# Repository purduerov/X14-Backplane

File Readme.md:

# Readme for X14-Backplane

Whenever you make a new part, download the datasheet and save it here _**and**_ with the part in the parts library

Always pull other people's changes before beginning to work
`git pull`

Be sure to push your changes after  working on them. Run:
1. `git add .` to add any files in this directory or a subdirectory
or `git add -u` to add any modified files
2. (Optional) `git clean -nX` to see what ignored files can be removed
	`git clean -fX` removes ignored files (Eagle backups)
3. `git commit -m "helpful commit message"` with a description of the work that you did
4. `git push` to push your work to github

Other helpful commands
* `git status` says information about modified and staged files
* `git log` shows the recent commits of the repository
* `git log filename.extension` show the recent commits for just that file
* `git checkout first-couple-letter-of-commit-id` lets you go back to a previous version
* `git checkout master` brings you back to the latest commit
* `git tag` lists the tags
* `git tag -a orderX -m "the version of the board placed for the X'th order"` tag a specific commit
* `git push --tags` needed to push tags to remote
* `git show orderX` show the commit log for the given tag
* `git checkout orderX` go back and interact with the files at the tagged commit

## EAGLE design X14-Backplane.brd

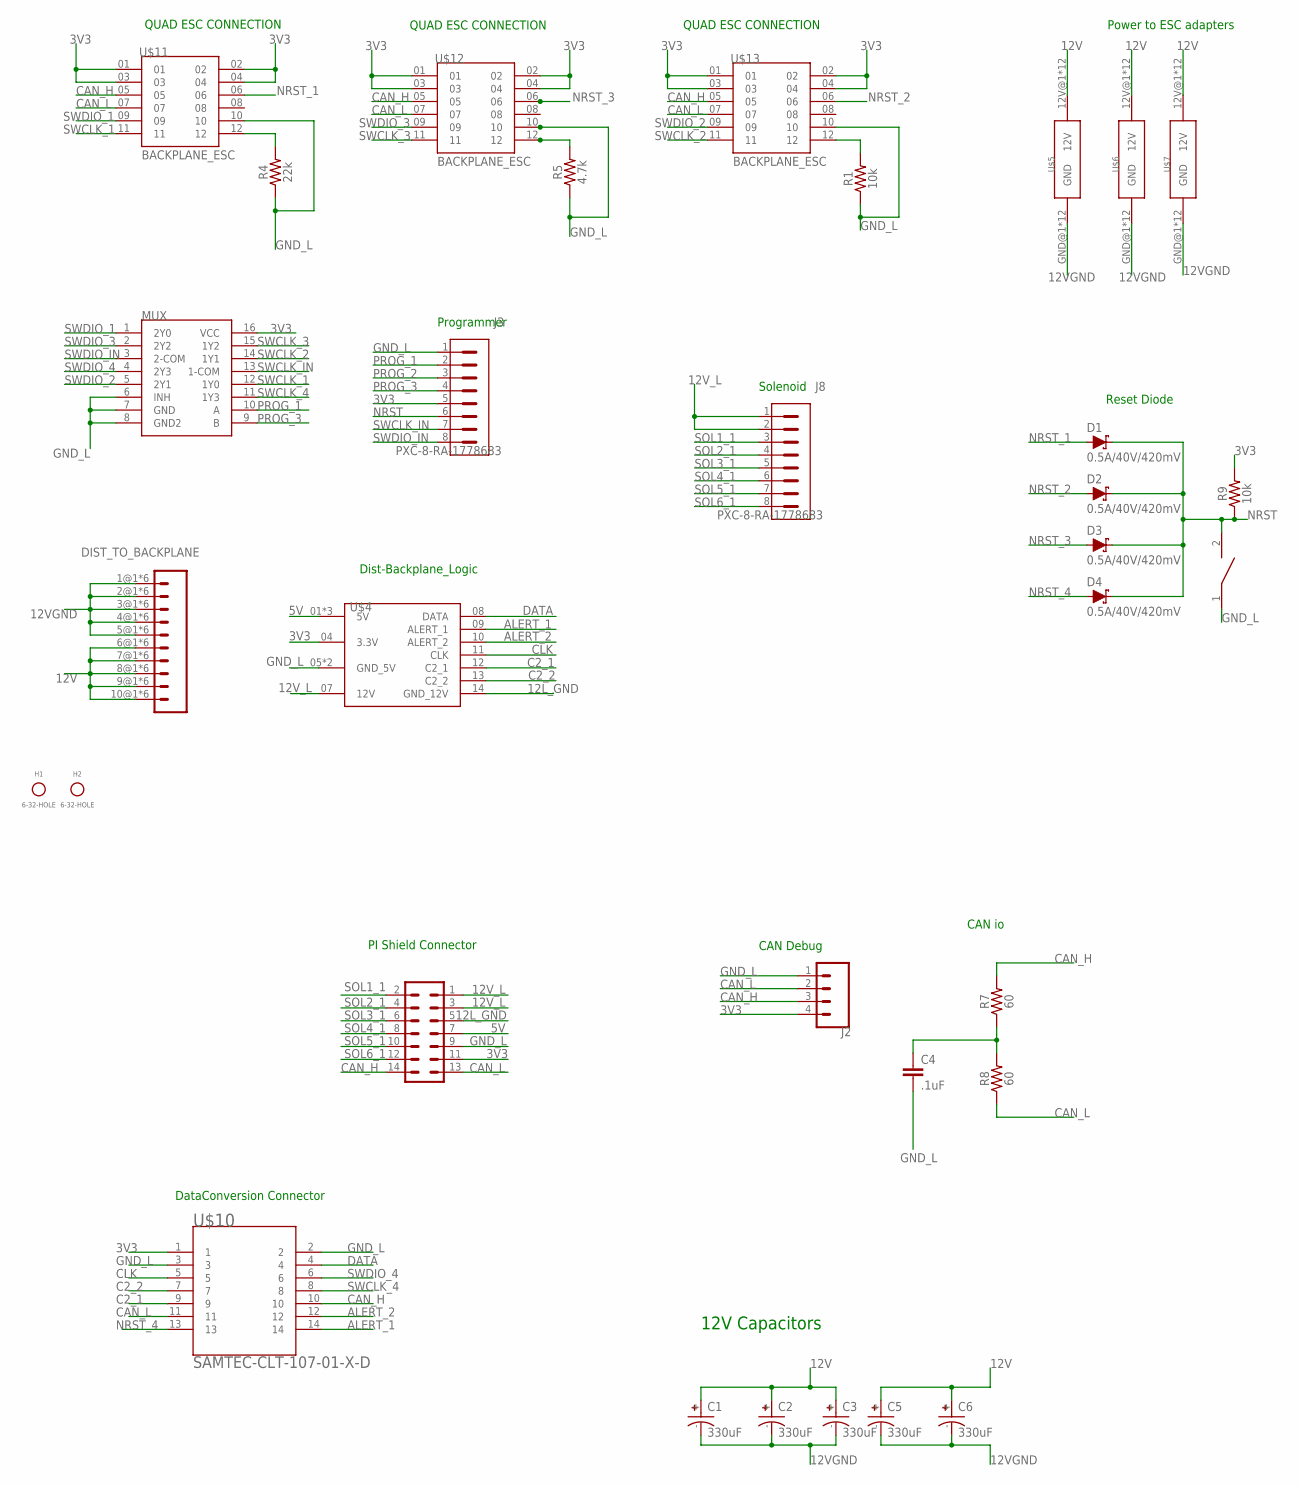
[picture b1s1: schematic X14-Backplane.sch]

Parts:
C1, C2, C3, C5, C6: 330uF; CAPAE1030X1050N
C4: .1uF; 0603
D1, D2, D3, D4: 0.5A/40V/420mV; SOD-323
DIST_TO_BACKPLANE: MPPT-10-01-01-L-RA-SD
H1, H2: 6-32-HOLE
J2: PXC-PTSM-04-RA-1778641
J3, J8: PXC-8-RA-1778683
MUX: TI-SN74LV4052A; SOIC-16
R1, R9: 10k; 0603
R4: 22k; 0603
R5: 4.7k; 0603
R7, R8: 60; 0603
U$4: BACKPLANE-DISTRIBUTION; SAMTEC_IPL1-107-01-X-D-K(B-D)
U$5, U$6, U$7: BACKPLANE_ESC_ADAPTER_PWRBKP; BACKPLANE_ESC_ADAPTER_BKP_PWR
U$8: DISCRETECOMPONENTS_SWITCH; DISCRETECOMPONENTS_SW_2512
U$9: 7X_CONN; IPL7X2
U$10: BACKPLANE->DATACONV; SAMTEC-CLT-107-01-X-D-BACKPLANE
U$11, U$12, U$13: BACKPLANE_ESC; SAMTEC_SQT-107-01-F-D

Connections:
3V3: J2.4, J3.5, MUX.16 (VCC), R9.2, U$4.04 (3.3V), U$9.11 (24), U$10.1, U$11.01, U$11.02, U$11.03, U$11.04, U$12.01, U$12.02, U$12.03, U$12.04, U$13.01, U$13.02, U$13.03, U$13.04
5V: U$4.01 (5V), U$4.02 (5V), U$4.03 (5V), U$9.7 (20)
12L_GND: U$4.14 (GND_12V), U$9.5 (18)
12V: C1.+, C2.+, C3.+, C5.+, C6.+, DIST_TO_BACKPLANE.6@1 (6), DIST_TO_BACKPLANE.6@2 (6), DIST_TO_BACKPLANE.6@3 (6), DIST_TO_BACKPLANE.6@4 (6), DIST_TO_BACKPLANE.6@5 (6), DIST_TO_BACKPLANE.6@6 (6), DIST_TO_BACKPLANE.7@1 (7), DIST_TO_BACKPLANE.7@2 (7), DIST_TO_BACKPLANE.7@3 (7), DIST_TO_BACKPLANE.7@4 (7), DIST_TO_BACKPLANE.7@5 (7), DIST_TO_BACKPLANE.7@6 (7), DIST_TO_BACKPLANE.8@1 (8), DIST_TO_BACKPLANE.8@2 (8), DIST_TO_BACKPLANE.8@3 (8), DIST_TO_BACKPLANE.8@4 (8), DIST_TO_BACKPLANE.8@5 (8), DIST_TO_BACKPLANE.8@6 (8), DIST_TO_BACKPLANE.9@1 (9), DIST_TO_BACKPLANE.9@2 (9), DIST_TO_BACKPLANE.9@3 (9), DIST_TO_BACKPLANE.9@4 (9), DIST_TO_BACKPLANE.9@5 (9), DIST_TO_BACKPLANE.9@6 (9), DIST_TO_BACKPLANE.10@1 (10), DIST_TO_BACKPLANE.10@2 (10), DIST_TO_BACKPLANE.10@3 (10), DIST_TO_BACKPLANE.10@4 (10), DIST_TO_BACKPLANE.10@5 (10), DIST_TO_BACKPLANE.10@6 (10), U$5.12V@1 (12V), U$5.12V@2 (12V), U$5.12V@3 (12V), U$5.12V@4 (12V), U$5.12V@5 (12V), U$5.12V@6 (12V), U$5.12V@7 (12V), U$5.12V@8 (12V), U$5.12V@9 (12V), U$5.12V@10 (12V), U$5.12V@11 (12V), U$5.12V@12 (12V), U$6.12V@1 (12V), U$6.12V@2 (12V), U$6.12V@3 (12V), U$6.12V@4 (12V), U$6.12V@5 (12V), U$6.12V@6 (12V), U$6.12V@7 (12V), U$6.12V@8 (12V), U$6.12V@9 (12V), U$6.12V@10 (12V), U$6.12V@11 (12V), U$6.12V@12 (12V), U$7.12V@1 (12V), U$7.12V@2 (12V), U$7.12V@3 (12V), U$7.12V@4 (12V), U$7.12V@5 (12V), U$7.12V@6 (12V), U$7.12V@7 (12V), U$7.12V@8 (12V), U$7.12V@9 (12V), U$7.12V@10 (12V), U$7.12V@11 (12V), U$7.12V@12 (12V)
12VGND: C1.-, C2.-, C3.-, C5.-, C6.-, DIST_TO_BACKPLANE.1@1 (1), DIST_TO_BACKPLANE.1@2 (1), DIST_TO_BACKPLANE.1@3 (1), DIST_TO_BACKPLANE.1@4 (1), DIST_TO_BACKPLANE.1@5 (1), DIST_TO_BACKPLANE.1@6 (1), DIST_TO_BACKPLANE.2@1 (2), DIST_TO_BACKPLANE.2@2 (2), DIST_TO_BACKPLANE.2@3 (2), DIST_TO_BACKPLANE.2@4 (2), DIST_TO_BACKPLANE.2@5 (2), DIST_TO_BACKPLANE.2@6 (2), DIST_TO_BACKPLANE.3@1 (3), DIST_TO_BACKPLANE.3@2 (3), DIST_TO_BACKPLANE.3@3 (3), DIST_TO_BACKPLANE.3@4 (3), DIST_TO_BACKPLANE.3@5 (3), DIST_TO_BACKPLANE.3@6 (3), DIST_TO_BACKPLANE.4@1 (4), DIST_TO_BACKPLANE.4@2 (4), DIST_TO_BACKPLANE.4@3 (4), DIST_TO_BACKPLANE.4@4 (4), DIST_TO_BACKPLANE.4@5 (4), DIST_TO_BACKPLANE.4@6 (4), DIST_TO_BACKPLANE.5@1 (5), DIST_TO_BACKPLANE.5@2 (5), DIST_TO_BACKPLANE.5@3 (5), DIST_TO_BACKPLANE.5@4 (5), DIST_TO_BACKPLANE.5@5 (5), DIST_TO_BACKPLANE.5@6 (5), U$5.GND@1 (GND), U$5.GND@2 (GND), U$5.GND@3 (GND), U$5.GND@4 (GND), U$5.GND@5 (GND), U$5.GND@6 (GND), U$5.GND@7 (GND), U$5.GND@8 (GND), U$5.GND@9 (GND), U$5.GND@10 (GND), U$5.GND@11 (GND), U$5.GND@12 (GND), U$6.GND@1 (GND), U$6.GND@2 (GND), U$6.GND@3 (GND), U$6.GND@4 (GND), U$6.GND@5 (GND), U$6.GND@6 (GND), U$6.GND@7 (GND), U$6.GND@8 (GND), U$6.GND@9 (GND), U$6.GND@10 (GND), U$6.GND@11 (GND), U$6.GND@12 (GND), U$7.GND@1 (GND), U$7.GND@2 (GND), U$7.GND@3 (GND), U$7.GND@4 (GND), U$7.GND@5 (GND), U$7.GND@6 (GND), U$7.GND@7 (GND), U$7.GND@8 (GND), U$7.GND@9 (GND), U$7.GND@10 (GND), U$7.GND@11 (GND), U$7.GND@12 (GND)
12V_L: J8.1, J8.2, U$4.07 (12V), U$9.1 (14), U$9.3 (16)
ALERT_1: U$4.09 (ALERT_1), U$10.14
ALERT_2: U$4.10 (ALERT_2), U$10.12
C2_1: U$4.12 (C2_1), U$10.9
C2_2: U$4.13 (C2_2), U$10.7
CAN_H: J2.3, R7.2, U$9.14 (2), U$10.10, U$11.05, U$12.05, U$13.05
CAN_L: J2.2, R8.1, U$9.13 (1), U$10.11, U$11.07, U$12.07, U$13.07
CLK: U$4.11 (CLK), U$10.5
DATA: U$4.08 (DATA), U$10.4
ESCID_1: R4.2, U$11.12
ESCID_2: R1.2, U$13.12
ESCID_3: R5.2, U$12.12
GND_L: C4.2, J2.1, J3.1, MUX.6 (INH), MUX.7 (GND), MUX.8 (GND2), R1.1, R4.1, R5.1, U$4.05 (GND_5V), U$4.06 (GND_5V), U$8.1, U$9.9 (22), U$10.2, U$10.3, U$11.10, U$12.10, U$13.10
unnamed: C4.1, R7.1, R8.2
NRST: D1.C, D2.C, D3.C, D4.C, J3.6, R9.1, U$8.2
NRST_1: D1.A, U$11.06
NRST_2: D2.A, U$13.06
NRST_3: D3.A, U$12.06
NRST_4: D4.A, U$10.13
PROG_1: J3.2, MUX.10 (A)
PROG_2: J3.3
PROG_3: J3.4, MUX.9 (B)
SOL1_1: J8.3, U$9.2 (13)
SOL2_1: J8.4, U$9.4 (15)
SOL3_1: J8.5, U$9.6 (17)
SOL4_1: J8.6, U$9.8 (19)
SOL5_1: J8.7, U$9.10 (21)
SOL6_1: J8.8, U$9.12 (23)
SWCLK_1: MUX.12 (1Y0), U$11.11
SWCLK_2: MUX.14 (1Y1), U$13.11
SWCLK_3: MUX.15 (1Y2), U$12.11
SWCLK_4: MUX.11 (1Y3), U$10.8
SWCLK_IN: J3.7, MUX.13 (1-COM)
SWDIO_1: MUX.1 (2Y0), U$11.09
SWDIO_2: MUX.5 (2Y1), U$13.09
SWDIO_3: MUX.2 (2Y2), U$12.09
SWDIO_4: MUX.4 (2Y3), U$10.6
SWDIO_IN: J3.8, MUX.3 (2-COM)

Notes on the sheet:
CAN Debug
Programmer
QUAD ESC CONNECTION
Dist-Backplane_Logic
Solenoid
Power to ESC adapters
Reset Diode
PI Shield Connector
CAN io
DataConversion Connector
12V Capacitors

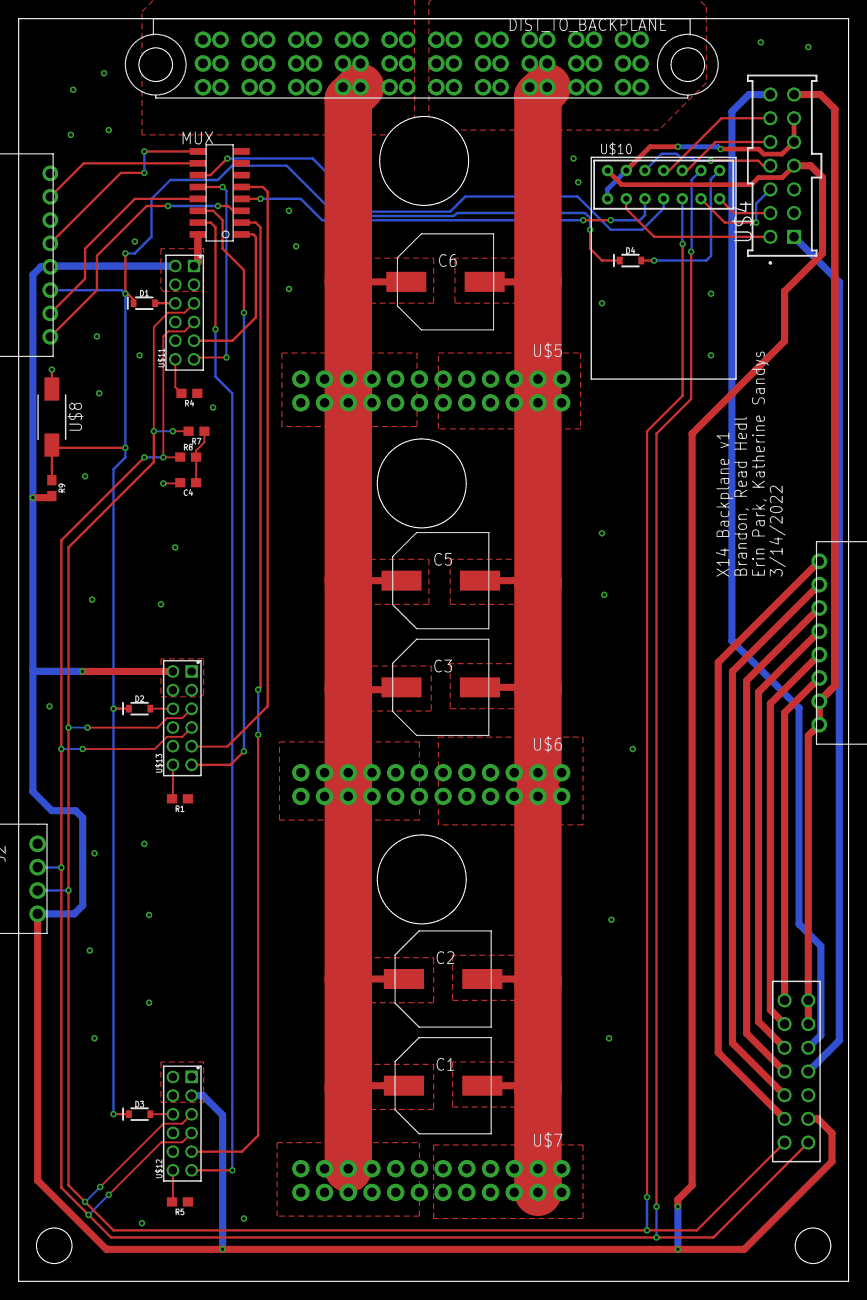
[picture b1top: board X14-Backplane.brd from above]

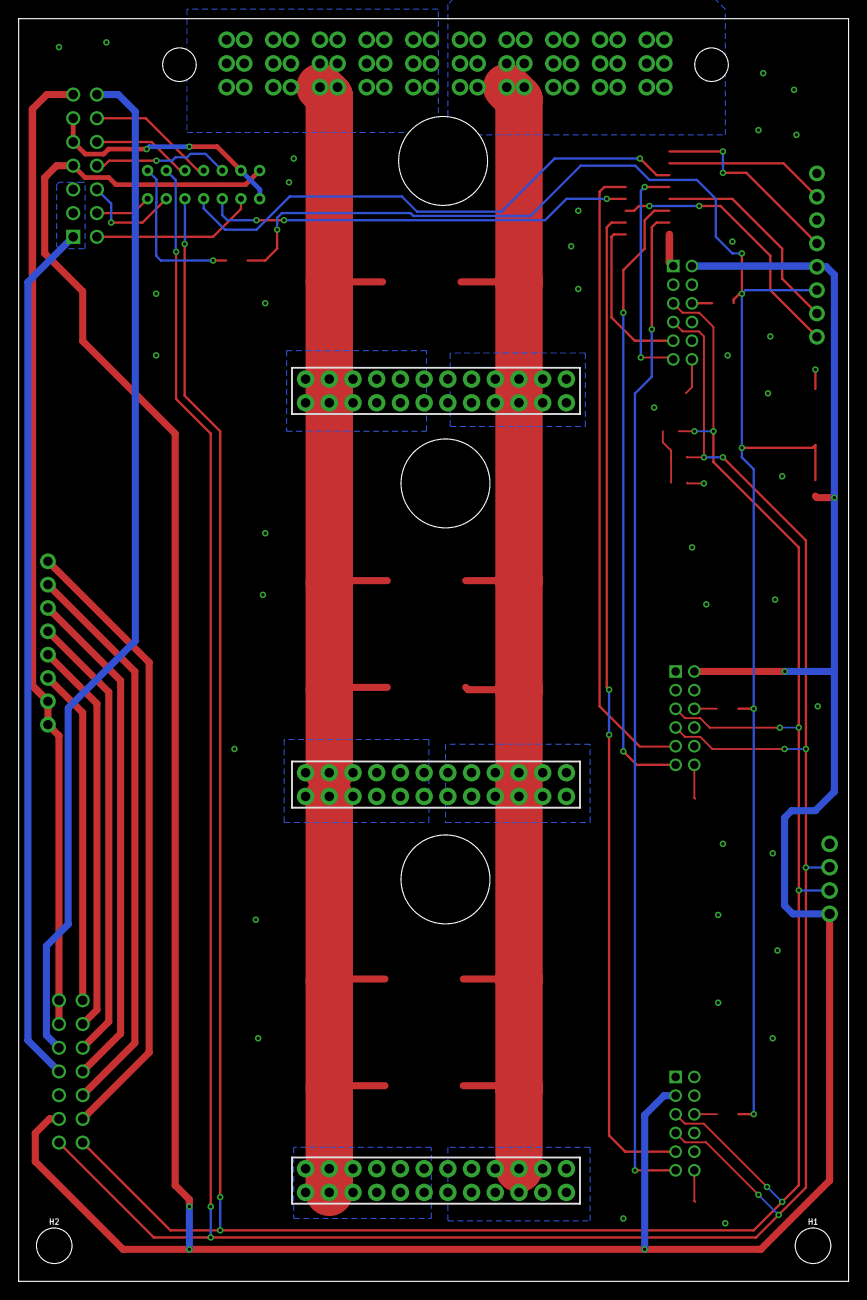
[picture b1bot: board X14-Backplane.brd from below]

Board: 2 copper layers, 88.9 x 135.3 mm, 33 parts (2 on the bottom side), 42 nets.

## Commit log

2021-09-18 readme+gitignore
2021-10-02 fixed readme
2021-10-20 Design Review X14-Backplane
    X14-Backplane for design review
2021-11-29 X14-Backplane 11/29
    This is the most up to date backplane as of 11/29/2021
2021-12-02 X14-Backplane 12/2
    Most up to date backplane as of 12/2/2021
2021-12-02 sfdgfhg
2021-12-02 Revert "sfdgfhg"
    This reverts commit 89fcb60d7aa2de489dc8c4b854d40a80c75a218c.
2021-12-03 X14-Backplane 12/2 #2
    This has more signals routed except from those from dist (top right of board) and the power between the ESC's
2021-12-04 X14-Backplane 12/4
    This is the most up to date version as of 12/4/2021
2021-12-04 routing
2021-12-30 rerouted board
2021-12-30 some adjustments
2021-12-31 afawevvew
2021-12-31 Implemented conversion board
2021-12-31 second round of edits to bkplane
2021-12-31 added ESC adapter holes and some capacitors
2022-01-02 TODO: Fix CAN line, Silkcreen
2022-01-03 todo: new cap, silkscreen
2022-01-07 Added Silkscreen, last cap
2022-01-07 almost ordered without the tstop polygon
2022-01-26 STEPS!
2022-03-10 new connector UwU SQT
2022-03-14 shrunk board to better fit in box for v2
2022-03-14 Step Export

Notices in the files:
parts and their libraries:
SparkFun-Capacitors: Licensing: Creative Commons ShareAlike 4.0 International - https://creativecommons.org/licenses/by-sa/4.0
